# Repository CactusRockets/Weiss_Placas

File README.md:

# Placa de Iluminação Weiss

Placa de acionamento de iluminação desenvolvida em **KiCad**, responsável por controlar dois LEDs com o objetivo de iluminar a parte interna do weiss através de uma chave (push-button), a partir de uma alimentação externa de **3.3V**. O projeto foi desenhado para ser simples e robusto, priorizando facilidade de montagem (todos os componentes em THT) e baixo custo.

## Visão geral do circuito

O circuito é alimentado externamente via um conector **JST XH de 2 vias**, que entrega +3.3V e GND à placa. Essa alimentação passa por um **push-button (SW1)**, que atua como chave liga/desliga geral do circuito. A partir do botão, a alimentação se divide em **dois ramos em paralelo**, cada um composto por um resistor limitador de corrente em série com um LED de alta potência:

Ou seja: quando o botão é pressionado (ou travado, dependendo do tipo de chave utilizada), o circuito fecha e os dois LEDs acendem simultaneamente. Cada LED possui seu próprio resistor, de forma que o brilho e a corrente de cada um são definidos de forma independente — isso evita que uma eventual diferença entre os dois LEDs (tensão direta, tolerância) afete o outro ramo, como aconteceria se estivessem em paralelo direto sob um único resistor.

Foram incluídas **PWR_FLAGs** no esquemático em +3.3V e GND. Elas não fazem parte do circuito fisicamente: servem apenas para informar ao ERC (Electrical Rules Checker) do KiCad que esses nós de alimentação são supridos por uma fonte externa (o JST), evitando falsos positivos de "net não alimentada".

## Componentes

| Referência | Componente | Footprint / Símbolo | Função |
|---|---|---|---|
| **JST1** | Conector JST XH 2 vias | `Connector_JST:JST_XH_B2B-XH-A_1x02_P2.50mm_Vertical` | Entrada de alimentação externa (+3.3V e GND) |
| **SW1** | Push-button | `Button_Switch_SMD:SW_SPST_B3S-1000` (footprint na placa: `SW_SPST_Omron_B3F-40xx-CRD`) | Chave de acionamento (liga/desliga) do circuito |
| **R1** | Resistor 15Ω | `Resistor_THT:R_Axial_DIN0204_L3.6mm_D1.6mm_P7.62mm_Horizontal` | Limitador de corrente do LED U1 |
| **R2** | Resistor 15Ω | `Resistor_THT:R_Axial_DIN0204_L3.6mm_D1.6mm_P7.62mm_Horizontal` | Limitador de corrente do LED U2 |
| **U1** | LED de alta potência | `LED_THT:LED_D5.0mm` | Iluminação (ramo 1) |
| **U2** | LED de alta potência | `LED_THT:LED_D5.0mm` | Iluminação (ramo 2) |

> Os símbolos `JST_basic`, `Push_button_4_pin` e `Led_High` são customizados e estão definidos na biblioteca local `CRD_KICAD.kicad_sym`, criada para padronizar os componentes usados nos projetos da Cactus Rockets.

## Funcionamento

O funcionamento da placa é puramente analógico/passivo — não há microcontrolador ou lógica embarcada:

1. A alimentação de +3.3V chega pelo conector **JST1**.
2. O **SW1** atua como interruptor: enquanto estiver fechado, a corrente flui para os dois ramos de LED.
3. Cada ramo (R + LED) limita a corrente que passa pelo respectivo LED, garantindo que ele opere dentro da faixa segura especificada pelo fabricante, evitando queima por excesso de corrente.
4. O retorno de ambos os ramos é feito para o **GND** comum da placa, que fecha o circuito de volta à fonte externa.

Por não haver controle ativo (PWM, microcontrolador, etc.), o brilho dos LEDs é fixo e definido unicamente pelo valor dos resistores e pela tensão de alimentação — não há dimerização nem controle remoto nesta versão da placa.

## Cálculo dos resistores limitadores

O valor do resistor limitador é definido pela equação pela lei de ohm:

```
R = (V_fonte - V_LED) / I_LED
```

Com `V_fonte = 3.3V` e `R = 15Ω`, a corrente em cada ramo depende da tensão direta (V_f) do LED utilizado. Por exemplo:

- Para um LED com V_f ≈ 2.0V → I ≈ (3.3 − 2.0) / 15 ≈ **87 mA**
- Para um LED com V_f ≈ 3.0V → I ≈ (3.3 − 3.0) / 15 ≈ **20 mA**

## Placa (PCB)

- Placa de **1.6mm** de espessura (FR4 padrão), com contorno definido em `Edge.Cuts`.
- Todos os componentes são **THT** (through-hole), facilitando a montagem manual e a soldagem.
- Footprints utilizados:
  - `CRD_Footprints:SW_SPST_Omron_B3F-40xx-CRD` (SW1)
  - `LED_THT:LED_D5.0mm` / `CRD_Footprints:LED_D5.0mm-CRD` (U1, U2)
  - `Resistor_THT:R_Axial_DIN0204_L3.6mm_D1.6mm_P7.62mm_Horizontal` (R1, R2)
  - `Connector_JST:JST_XH_B2B-XH-A_1x02_P2.50mm_Vertical` (JST1)

## Arquivos do projeto

| Arquivo | Descrição |
|---|---|
| `Placa_de_Iluminação_Weiss.kicad_sch` | Esquemático elétrico da placa |
| `Placa_de_Iluminação_Weiss.kicad_pcb` | Layout da placa (PCB) |
| `Placa_de_Iluminação_Weiss.kicad_pro` | Arquivo de projeto do KiCad |
| `CRD_KICAD.kicad_sym` | Biblioteca de símbolos customizados da Cactus Rockets |
| `fp-lib-table` | Tabela de bibliotecas de footprints usadas no projeto |

# Placa de Processamento — Weiss

Placa eletrônica central do projeto **Weiss**, desenvolvida em **KiCad**, responsável por concentrar o processamento, a aquisição de dados, o armazenamento local e as interfaces de telemetria e sinalização do sistema.

O projeto utiliza um **ESP32 DevKit V1** como controlador principal e integra módulos de rádio LoRa, GPS, cartão microSD, barômetro, unidade inercial, buzzer, LED de status e conectores para sinais externos.

> **Atenção:** esta documentação foi levantada a partir do esquemático e do layout da placa. Antes da fabricação ou da integração ao veículo, execute ERC/DRC no KiCad e confira a pinagem com o firmware e com os módulos físicos utilizados.

## Visão geral

Principais recursos:

- ESP32 DevKit V1 como unidade de processamento;
- telemetria por módulo LoRa **E22-400T30D**;
- posicionamento por módulo GPS serial;
- registro de dados em cartão microSD via SPI;
- medição de pressão e altitude com **BMP390** via I²C;
- medição inercial com **MPU6050** via I²C;
- buzzer e LED para sinalização local;
- duas entradas provenientes de optoacopladores externos;
- duas linhas de interface identificadas como `SKIB1` e `SKIB2`;
- alimentação por bateria de 9 V, com chave e duas linhas reguladas de 5 V;
- conectores JST de 2 vias para alimentação e sinais auxiliares.

## Arquitetura elétrica

```mermaid
flowchart LR
    B["Bateria 9 V"] --> S["Chave SS-5GL"]
    S --> VIN["VIN"]
    VIN --> R1["Regulador 5 V — VOUT"]
    VIN --> R2["Regulador 5 V — VOUT_LORA"]
    R1 --> ESP["ESP32 DevKit V1"]
    R2 --> LORA["LoRa E22-400T30D"]
    ESP --> V33["Barramento 3,3 V"]
    V33 --> GPS["GPS"]
    V33 --> I2C["BMP390 + MPU6050"]
    V33 --> SD["microSD"]
    ESP <--> LORA
    ESP <--> GPS
    ESP <--> I2C
    ESP <--> SD
```

A chave `U$12` conecta o terminal comum `VIN` ao contato associado a `V_BATTERY`; o outro contato da chave aparece sem conexão no esquemático. A partir de `VIN`, dois reguladores independentes, ambos identificados como **5 V**, geram:

- `VOUT`: alimentação do pino `VIN` do ESP32 DevKit V1;
- `VOUT_LORA`: alimentação dedicada do módulo LoRa.

O barramento de **3,3 V** é distribuído a partir do pino `3V3` do ESP32 para os sensores, GPS, microSD e conectores auxiliares. Todos os subsistemas da placa compartilham o mesmo GND.

## Mapeamento de pinos do ESP32

| GPIO | Rede | Interface / função |
|---:|---|---|
| 2 | `LED1` | LED de status |
| 4 | `TX1` | TX do ESP32 para RX do GPS |
| 5 | `CS` | Chip Select do microSD |
| 12 | `SKIB2` | Linha externa SKIB2 |
| 13 | `SKIB1` | Linha externa SKIB1 |
| 14 | `BUZZER` | Acionamento do buzzer |
| 15 | `RX1` | RX do ESP32 vindo do TX do GPS |
| 16 | `RX2` | RX do ESP32 vindo do TXD do LoRa |
| 17 | `TX2` | TX do ESP32 para RXD do LoRa |
| 18 | `CLK` | Clock SPI do microSD |
| 19 | `MISO` | Dados SPI do microSD para o ESP32 |
| 21 | `SDA` | Dados do barramento I²C |
| 22 | `SCL` | Clock do barramento I²C |
| 23 | `MOSI` | Dados SPI do ESP32 para o microSD |
| 32 | `M1` | Seleção de modo do LoRa |
| 33 | `M0` | Seleção de modo do LoRa |
| 34 | `OPTOACOPLADOR2` | Entrada externa isolada |
| 35 | `OPTOACOPLADOR1` | Entrada externa isolada |

> Os GPIOs 34 e 35 do ESP32 são somente de entrada. As linhas `SKIB1` e `SKIB2` chegam diretamente ao ESP32 no esquema apresentado; elas são sinais lógicos e **não devem acionar cargas pirotécnicas diretamente**. Qualquer carga desse tipo exige estágio externo de potência, intertravamentos e isolamento apropriados.

## Interfaces dos módulos

### LoRa E22-400T30D

| Pino do módulo | Rede da placa | Destino |
|---|---|---|
| `VCC` | `VOUT_LORA` | Alimentação dedicada de 5 V |
| `GND` | `GND` | Referência comum |
| `TXD` | `RX2` | GPIO16 do ESP32 |
| `RXD` | `TX2` | GPIO17 do ESP32 |
| `M0` | `M0` | GPIO33 do ESP32 |
| `M1` | `M1` | GPIO32 do ESP32 |
| `AUX` | Sem conexão | Reservado no layout atual |

### GPS

| Pino do módulo | Rede da placa | Destino |
|---|---|---|
| `VCC` | `3V3` | Alimentação de 3,3 V |
| `GND` | `GND` | Referência comum |
| `RX` | `TX1` | GPIO4 do ESP32 |
| `TX` | `RX1` | GPIO15 do ESP32 |

### BMP390 e MPU6050

Os dois sensores compartilham o barramento I²C:

| Sinal | GPIO do ESP32 | Módulos |
|---|---:|---|
| `SDA` | 21 | BMP390 e MPU6050 |
| `SCL` | 22 | BMP390 e MPU6050 |
| `3V3` | — | Alimentação |
| `GND` | — | Referência comum |

No layout atual, os pinos auxiliares `CS`, `SDO` e `INT` do BMP390 e `XDA`, `XCL`, `ADO` e `INT` do MPU6050 não são utilizados.

### Cartão microSD

| Sinal | GPIO do ESP32 |
|---|---:|
| `CS` | 5 |
| `CLK` | 18 |
| `MISO` | 19 |
| `MOSI` | 23 |
| `VCC` | 3,3 V |
| `GND` | GND |

## Conectores auxiliares

| Referência | Identificação | Pino 1 | Pino 2 |
|---|---|---|---|
| `U$10` | Bateria 9 V | `V_BATTERY` | `GND` |
| `U$6` | Skibs | `SKIB1` | `SKIB2` |
| `U$7` | Optoacopladores | `OPTOACOPLADOR1` | `OPTOACOPLADOR2` |
| `U$4` | Buzzer / 3,3 V | `BUZZER` | `3V3` |
| `U$5` | GND / 3,3 V | `3V3` | `GND` |

## Componentes principais

| Referência | Componente | Função |
|---|---|---|
| `U$11` | ESP32 DevKit V1 | Processamento e controle das interfaces |
| `U$2` | E22-400T30D | Comunicação LoRa |
| `U$3` | GPS Module | Posicionamento e referência de tempo |
| `U$1` | BMP390 | Pressão atmosférica e altitude |
| `U$9` | MPU6050 | Acelerômetro e giroscópio |
| `U$8` | MicroSD Small Reader | Armazenamento local de dados |
| `IC1` | Regulador 5 V | Alimentação `VOUT` do ESP32 |
| `IC2` | Regulador 5 V | Alimentação `VOUT_LORA` |
| `U$12` | Chave SS-5GL | Comutação da alimentação de entrada |
| `SP1` | AL60P | Buzzer |
| `LED1` | LED vermelho 5 mm | Indicação visual |
| `R1` | 220 Ω | Limitação de corrente do LED |
| `R2` | 46 Ω | Componente auxiliar; o pad 2 está sem conexão funcional no layout atual |
| `U$4` a `U$7`, `U$10` | JST 2,54 mm, 2 vias | Alimentação e sinais externos |

## Dimensões e construção da PCB

- dimensões aproximadas do contorno: **150 × 80 mm**;
- espessura configurada: **1,6 mm**;
- placa de duas camadas de cobre (`F.Cu` e `B.Cu`);
- componentes predominantemente THT e módulos montados por barras de pinos;
- planos de cobre e trilhas de alimentação de maior largura;
- footprints personalizados disponíveis na biblioteca local `Weiss.pretty`.

## Arquivos do projeto

| Caminho | Descrição |
|---|---|
| `Esquema.kicad_pro` | Projeto principal do KiCad |
| `Esquema.kicad_sch` | Esquemático elétrico |
| `Esquema.kicad_pcb` | Layout da PCB |
| `Esquema.svg` | Exportação vetorial do esquemático |
| `Esquema.kicad_dru` | Regras personalizadas da placa |
| `Weiss.pretty/` | Biblioteca local de footprints |
| `BibliotecasCRD-KiCad-main/` | Bibliotecas auxiliares utilizadas pelo projeto |
| `fp-lib-table` | Tabela de bibliotecas de footprints |
| `sym-lib-table` | Tabela de bibliotecas de símbolos |

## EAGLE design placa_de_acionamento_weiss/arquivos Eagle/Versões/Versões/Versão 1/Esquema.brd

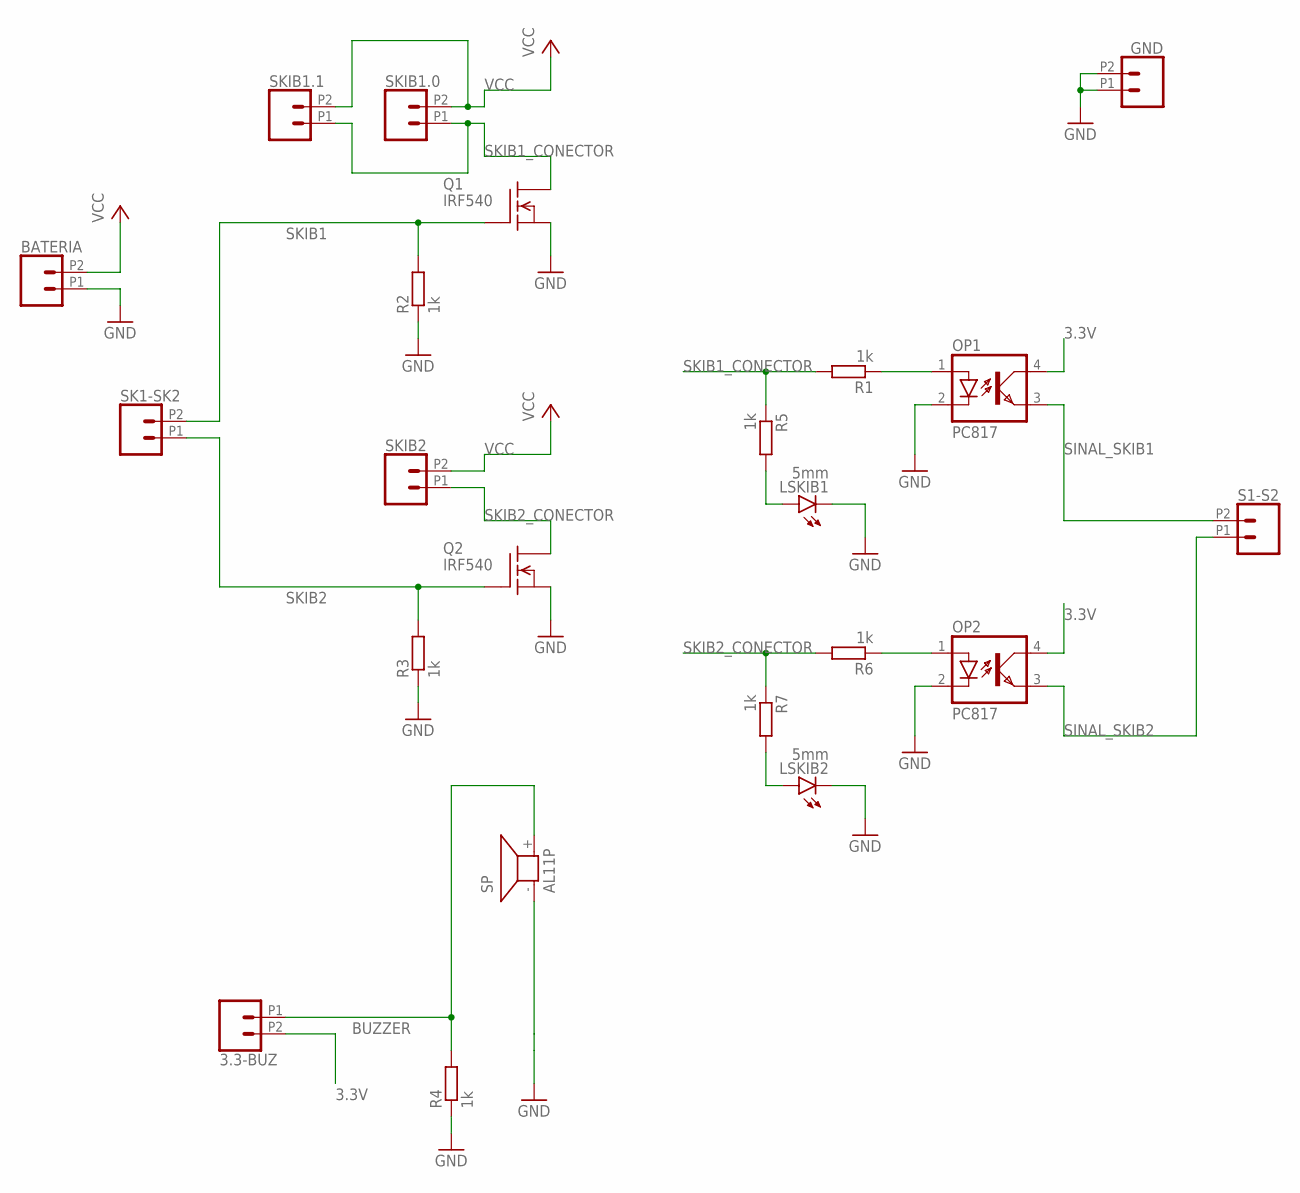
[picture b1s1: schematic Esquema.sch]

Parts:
3.3-BUZ: CONN_022.54MM_SCREWTERM; 1X02_2.54_SCREWTERM
BATERIA: CONN_022.54MM_SCREWTERM; 1X02_2.54_SCREWTERM
GND: CONN_022.54MM_SCREWTERM; 1X02_2.54_SCREWTERM
LSKIB1, LSKIB2: 5mm; LED5MM
OP1, OP2: PC817; DIL04
Q1, Q2: IRF540; TO220
R1, R2, R3, R4, R5, R6, R7: 1k; 0207/10
S1-S2: CONN_022.54MM_SCREWTERM; 1X02_2.54_SCREWTERM
SK1-SK2: CONN_022.54MM_SCREWTERM; 1X02_2.54_SCREWTERM
SKIB1.0, SKIB1.1, SKIB2: CONN_022.54MM_SCREWTERM; 1X02_2.54_SCREWTERM
SP: AL11P

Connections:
3.3V: 3.3-BUZ.P2 (2), OP1.4 (COL), OP2.4 (COL)
BUZZER: 3.3-BUZ.P1 (1), R4.2, SP.+ (2)
GND: BATERIA.P1 (1), GND.P1 (1), GND.P2 (2), LSKIB1.K (C), LSKIB2.K (C), OP1.2 (C), OP2.2 (C), Q1.3 (S), Q2.3 (S), R2.1, R3.1, R4.1, SP.- (1)
unnamed: LSKIB2.A, R7.2
unnamed: LSKIB1.A, R5.2
unnamed: OP1.1 (A), R1.1
unnamed: OP2.1 (A), R6.1
SINAL_SKIB1: OP1.3 (EMIT), S1-S2.P2 (2)
SINAL_SKIB2: OP2.3 (EMIT), S1-S2.P1 (1)
SKIB1: Q1.1 (G), R2.2, SK1-SK2.P2 (2)
SKIB1_CONECTOR: Q1.2 (D), R1.2, R5.1, SKIB1.0.P1 (1), SKIB1.1.P1 (1)
SKIB2: Q2.1 (G), R3.2, SK1-SK2.P1 (1)
SKIB2_CONECTOR: Q2.2 (D), R6.2, R7.1, SKIB2.P1 (1)
VCC: BATERIA.P2 (2), SKIB1.0.P2 (2), SKIB1.1.P2 (2), SKIB2.P2 (2)

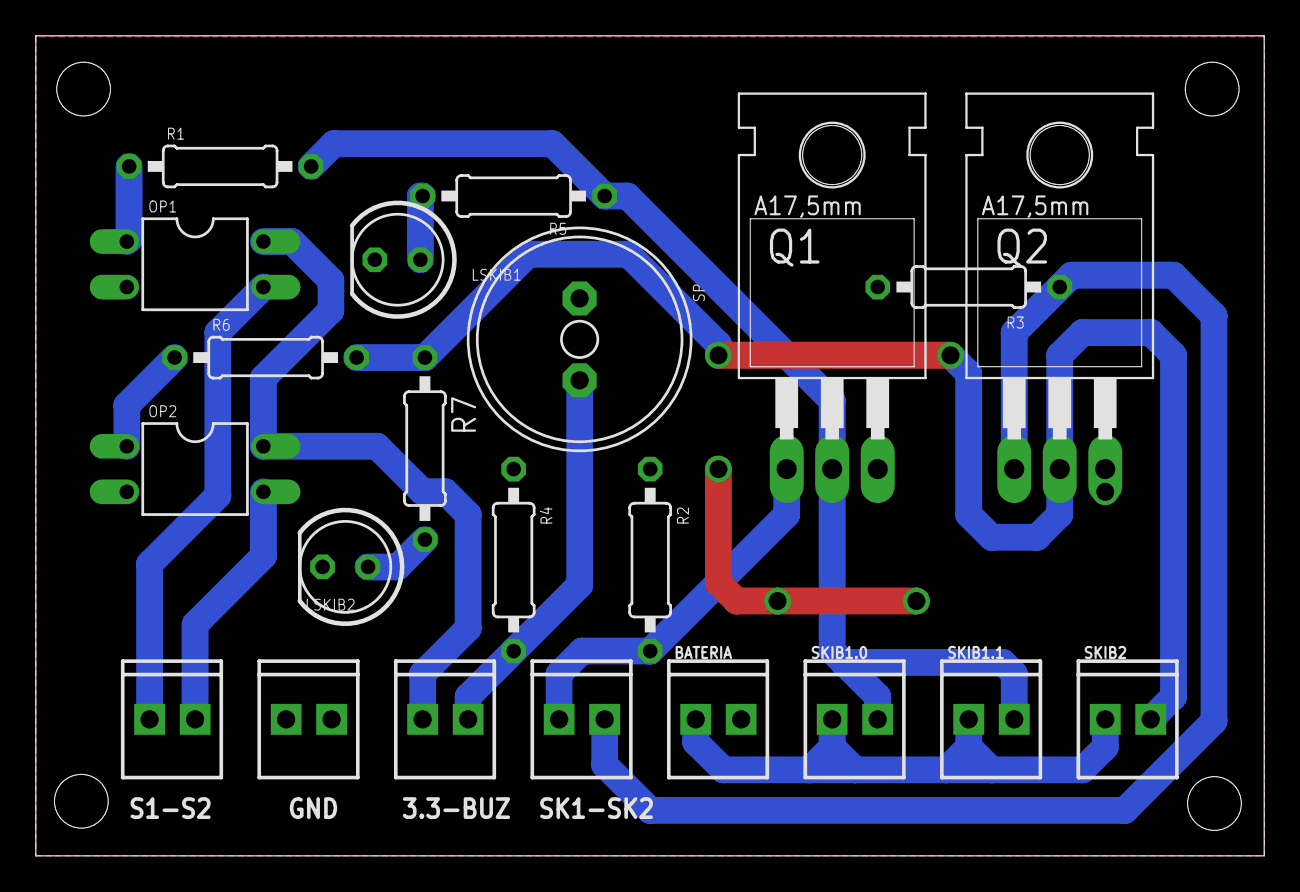
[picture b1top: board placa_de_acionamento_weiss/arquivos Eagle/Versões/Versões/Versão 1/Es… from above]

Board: 2 copper layers, 68.6 x 45.8 mm, 22 parts (0 on the bottom side), 14 nets.

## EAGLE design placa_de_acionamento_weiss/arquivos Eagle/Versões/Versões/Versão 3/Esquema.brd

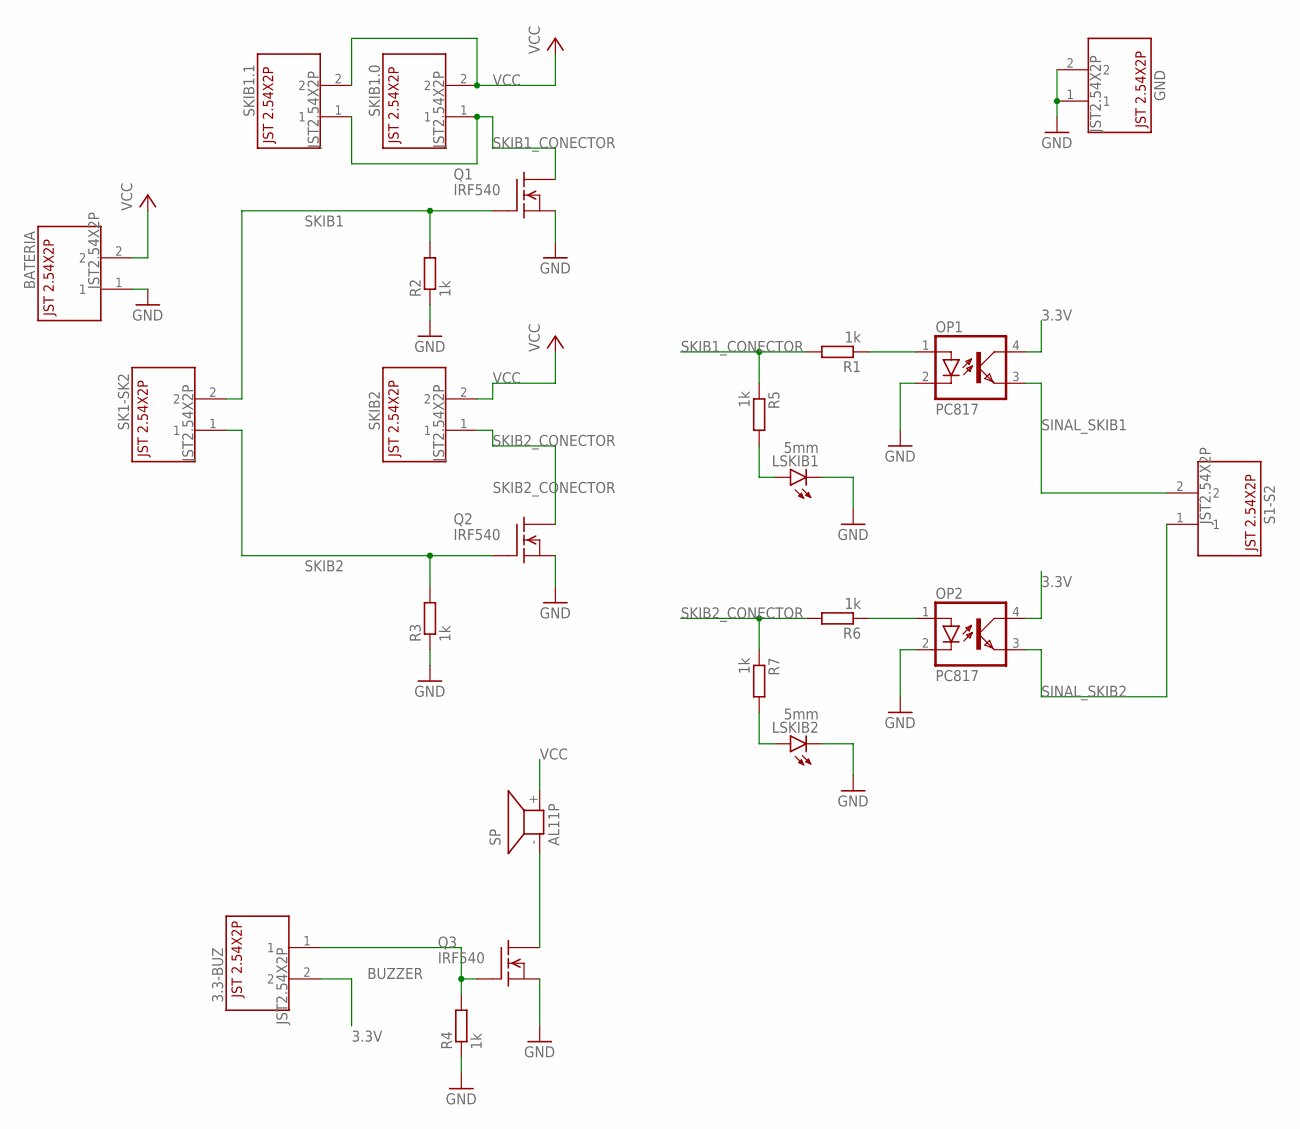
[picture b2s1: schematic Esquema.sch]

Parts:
3.3-BUZ: JST2.54X2P; JST2.54X2P_FOOTPRINT
BATERIA: JST2.54X2P; JST2.54X2P_FOOTPRINT
GND: JST2.54X2P; JST2.54X2P_FOOTPRINT
LSKIB1, LSKIB2: 5mm; LED5MM
OP1, OP2: PC817; DIL04
Q1, Q2, Q3: IRF540; TO220
R1, R2, R3, R4, R5, R6, R7: 1k; 0207/10
S1-S2: JST2.54X2P; JST2.54X2P_FOOTPRINT
SK1-SK2: JST2.54X2P; JST2.54X2P_FOOTPRINT
SKIB1.0, SKIB1.1, SKIB2: JST2.54X2P; JST2.54X2P_FOOTPRINT
SP: AL11P

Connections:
3.3V: 3.3-BUZ.2, OP1.4 (COL), OP2.4 (COL)
BUZZER: 3.3-BUZ.1, Q3.1 (G), R4.2
GND: BATERIA.1, GND.1, GND.2, LSKIB1.K (C), LSKIB2.K (C), OP1.2 (C), OP2.2 (C), Q1.3 (S), Q2.3 (S), Q3.3 (S), R2.1, R3.1, R4.1
unnamed: LSKIB2.A, R7.2
unnamed: Q3.2 (D), SP.- (1)
unnamed: LSKIB1.A, R5.2
unnamed: OP1.1 (A), R1.1
unnamed: OP2.1 (A), R6.1
SINAL_SKIB1: OP1.3 (EMIT), S1-S2.2
SINAL_SKIB2: OP2.3 (EMIT), S1-S2.1
SKIB1: Q1.1 (G), R2.2, SK1-SK2.2
SKIB1_CONECTOR: Q1.2 (D), R1.2, R5.1, SKIB1.0.1, SKIB1.1.1
SKIB2: Q2.1 (G), R3.2, SK1-SK2.1
SKIB2_CONECTOR: Q2.2 (D), R6.2, R7.1, SKIB2.1
VCC: BATERIA.2, SKIB1.0.2, SKIB1.1.2, SKIB2.2, SP.+ (2)

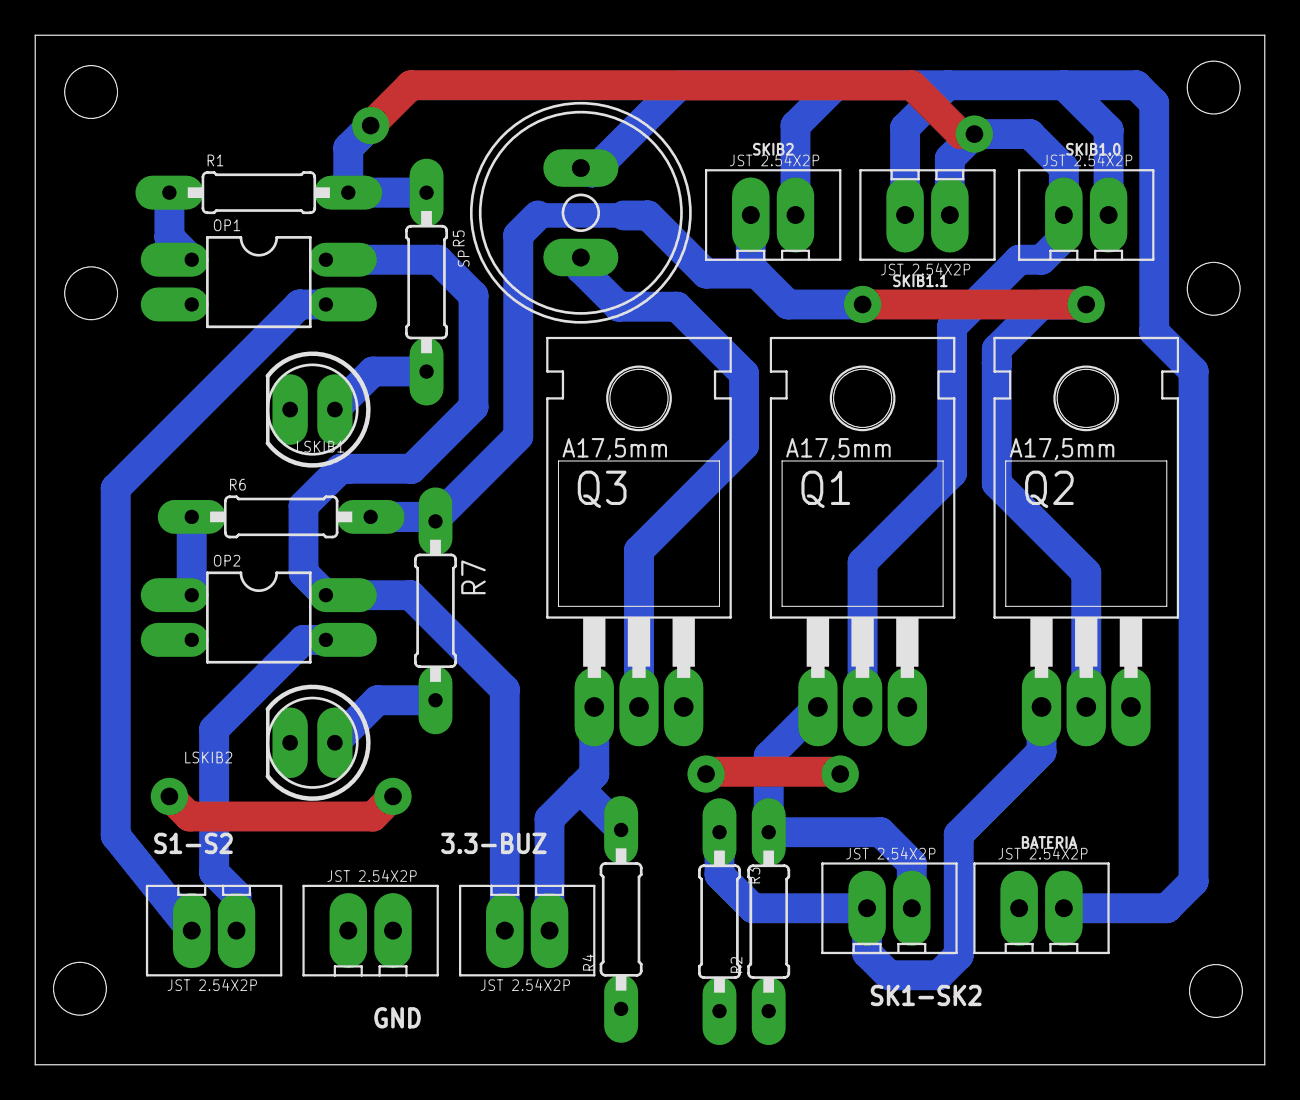
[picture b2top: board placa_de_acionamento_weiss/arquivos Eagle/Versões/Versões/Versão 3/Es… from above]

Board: 2 copper layers, 69.8 x 58.5 mm, 23 parts (0 on the bottom side), 15 nets.

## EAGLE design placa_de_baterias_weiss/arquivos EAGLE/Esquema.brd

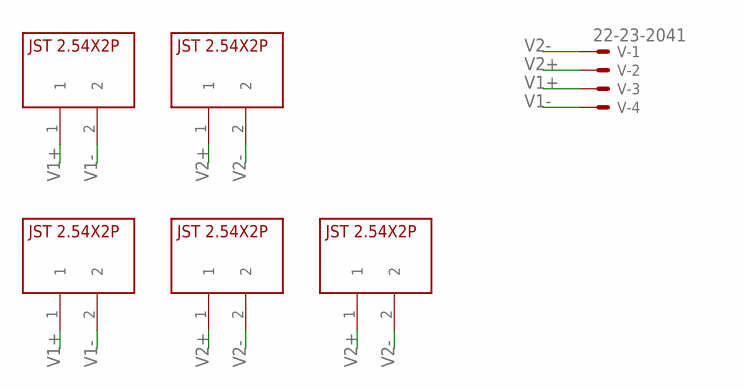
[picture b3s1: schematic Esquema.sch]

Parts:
U$1, U$2, U$3, U$4, U$5: JST2.54X2P; JST2.54X2P_FOOTPRINT
V: 22-23-2041

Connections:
V1+: U$1.1, U$4.1, V.3
V1-: U$1.2, U$4.2, V.4
V2+: U$2.1, U$3.1, U$5.1, V.2
V2-: U$2.2, U$3.2, U$5.2, V.1

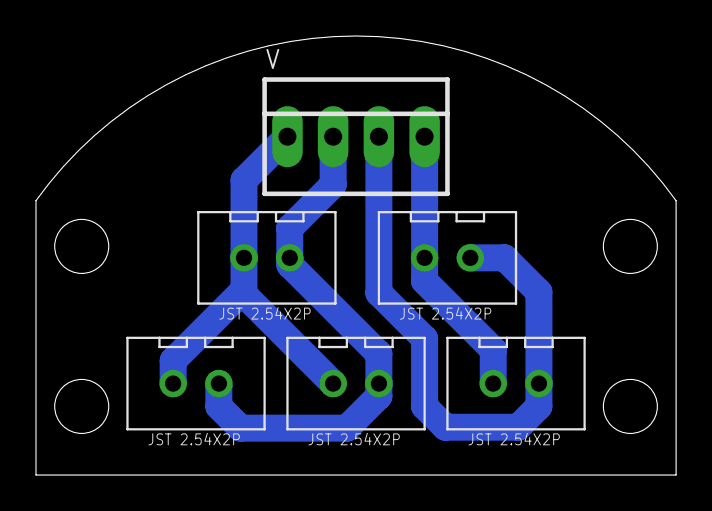
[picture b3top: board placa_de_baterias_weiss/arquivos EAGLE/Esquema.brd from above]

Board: 2 copper layers, 35.6 x 24.4 mm, 6 parts (0 on the bottom side), 4 nets.

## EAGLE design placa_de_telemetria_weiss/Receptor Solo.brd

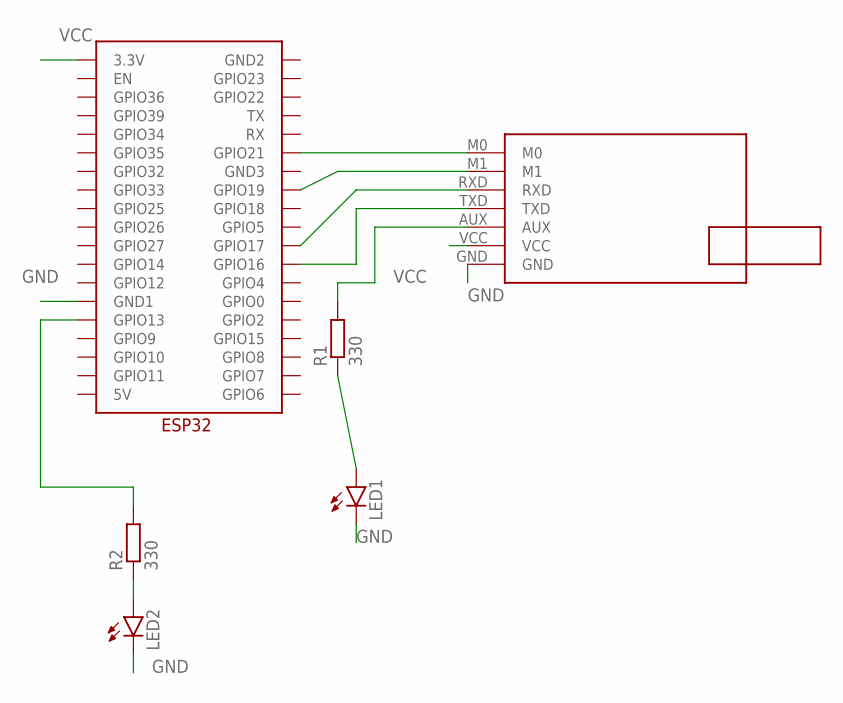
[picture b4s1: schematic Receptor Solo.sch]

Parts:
LED1, LED2: LED5MM
R1, R2: 330; 0207/10
U$1: ESP32
U$2: E22-400T30D; E22-400T30D_FOOTPRINT

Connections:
GND: LED1.K (C), LED2.K (C), U$1.GND1, U$2.GND
unnamed: U$1.GPIO21, U$2.M0
unnamed: U$1.GPIO19, U$2.M1
unnamed: U$1.GPIO17, U$2.RXD
unnamed: U$1.GPIO16, U$2.TXD
unnamed: R2.2, U$1.GPIO13
unnamed: R1.2, U$2.AUX
unnamed: LED1.A, R1.1
unnamed: LED2.A, R2.1
VCC: U$1.3.3V, U$2.VCC

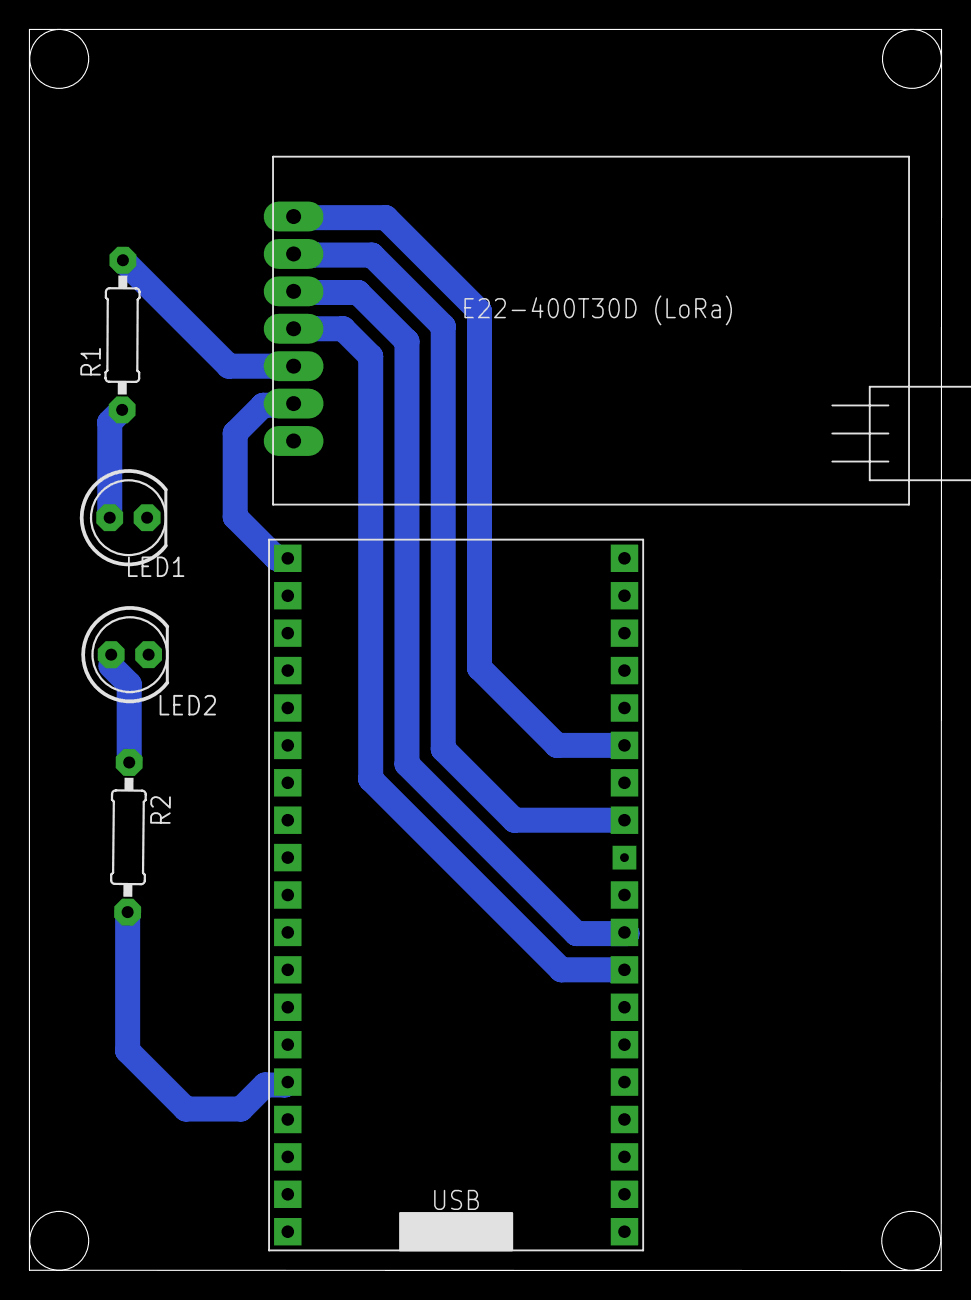
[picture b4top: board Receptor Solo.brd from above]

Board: 2 copper layers, 61.9 x 84.3 mm, 6 parts (0 on the bottom side), 10 nets.

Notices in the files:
parts and their libraries:
SparkFun-Connectors: Licensing: Creative Commons ShareAlike 4.0 International - https://creativecommons.org/licenses/by-sa/4.0
